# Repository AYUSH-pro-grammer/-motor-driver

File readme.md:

# STM32 Four Motor Driver

In my motor driver board, there is an STM32G431CBU6 with eight BTS7960B ICs to drive the four brushed DC motors.
I designed the circuit schematic and 4-layer PCB in KiCad, put artwork on both sides and wrote a simple Arduino sketch to check the hardware for the first time.

The repository contains the circuit schematic, PCB layout, Gerber files, parts list and demo firmware.
The board is currently in the design phase and needs to be assembled and tested.

## how it works

Each motor is connected between the outputs of two BTS7960B half-bridges
The STM32 provides one PWM signal and two direction signals per channel, which are combined using SN74ACT08 gates before going to the driver's inputs

The battery for the motors is plugged in via the XT60 connector, whereas the logic input is fed from 5V_IN
AMS1117-3.3 generates 3V3_MCU power supply for STM32

~~~text
STM32 PWM + direction --> SN74ACT08 gates --> BTS7960B pairs --> four motors
battery input --> motor supply
logic input --> 5V_IN --> AMS1117-3.3 --> STM32
encoder headers --> STM32
STM32 --> UART, I2C and external CAN transceiver header
~~~

there are four encoder connectors, a battery voltage divider, and three status LEDs in the circuit diagram.
the CAN bus requires a header connector that connects to an external transceiver module, but it is yet to be chosen.

## main features

- Four channels of motor control with two BTS7960B ICs on each channel
- Bare STM32G431CBU6 microcontroller in QFN packaging
- Two SN74ACT08 logic ICs for PWM and direction control of the motors
- 4-layer PCB approximately 162.5 x 57.4mm in size with a 1.6mm board thickness
- Screw terminal for motor outputs and XT60 footprint for battery input
- Connections to encoder, UART, I2C, and CAN module
- Front and back silkscreen printing
- UART controlled demo firmware with small motor pulses

## images

**full schematic**

**routed PCB**

**back artwork**

**angled board view**

these images are KiCad design previews, physical fit and operation still need checking on the assembled board

## how i plan to build it

1. check the supply connections, programming access and any remaining schematics and PCB checks
2. check that all BOM parts fit their footprints and select the regulator output capacitor
3. recreate and verify the Gerber and drill files following any modifications to the PCB
4. assemble the power and control boards and verify the supply rail voltages
5. program the demo using SWD and verify the control signals
6. test each motor channel one at a time using a current limited power supply

## firmware demo

open [motor_test.ino](firmware/motor_test/motor_test.ino) with the STM32duino Arduino core and select the generic STM32G431CBU board
the sketch uses the saved PCB pin mapping

| motor | PWM | direction 1 | direction 2 |
|---|---|---|---|
| A | PC6 | PB12 | PA10 |
| B | PB14 | PB15 | PB13 |
| C | PB4 | PB3 | PB5 |
| D | PA7 | PC4 | PB0 |

The UART console will use PB10 as TX and PB11 as RX at 115200 baud
Connect a 3.3 V USB-UART adapter where RX connects to PB10, TX to PB11 and GND to ground of the board

Send “a”, “b”, “c” or “d” to move forward and “A”, “B”, “C” or “D” to move backwards
Each command initiates one 500 ms pulse with a PWM value of 40/255 which is equal to 16%
Use “s” to stop before completion. The sketch begins with all outputs set to LOW

The demo sketch has yet to be compiled and tested on hardware, more tests with encoders and communication will be done later on

[STM32duino core and supported boards](https://github.com/stm32duino/Arduino_Core_STM32)

## what is in the repo

~~~text
.
├── firmware/motor_test/  Arduino motor test sketch
├── gerber/              PCB layers and drill files
├── gerber.zip           Fabrication archive
├── image/               Final project views and preserved originals
├── journal/             Individual devlogs and original screenshots
├── journal image/       Images used by the combined journal
├── kicad/               Schematic, PCB and project symbol library
├── bom.csv              Parts, quantities, prices and purchase links
├── JOURNAL.md           Combined development journal
└── readme.md            Project overview
~~~

## parts and BOM

the budget cost of the current parts is **$88.28 USD**, which includes the **PCB** at **$30.80** for five boards
the component totals refer to one board, while the orders include the quantities of components due to the vendor’s minimums
one 40-pin strip is ordered for cutting into eight headers

the prices are from the BOM estimates, with the conversion rate for ₹93.765 per USD for BTS7960
the shipping charges, additional taxes and the purchase of the C20 if necessary have to be added
C20 has a candidate link while the regulator compatibility check is underway

| board qty | order qty | part | unit price (USD) | cost (USD) | source |
|---:|---:|---|---:|---:|---|
| 11 | 50 | 100 nF 50 V X7R capacitor, 0805 | $0.0060 | $0.30 | [listing](https://www.lcsc.com/product-detail/C1711.html) |
| 4 | 4 | 1000 µF 25 V aluminum capacitor, SMD 10 × 10.5 mm | $0.4038 | $1.62 | [listing](https://www.lcsc.com/product-detail/C51018391.html) |
| 1 | 50 | 10 nF 50 V X7R capacitor, 0805 | $0.0116 | $0.58 | [listing](https://www.lcsc.com/product-detail/C1710.html) |
| 2 | 10 | 1 µF 50 V X7R capacitor, 0805 | $0.0403 | $0.40 | [listing](https://www.lcsc.com/product-detail/C28323.html) |
| 1 | 1 | 4.7 µF 25 V X5R capacitor, 0805 | $0.1300 | $0.13 | [listing](https://www.digikey.com/en/products/detail/samsung-electro-mechanics/CL21A475KAQNNNE/3889330) |
| 1 | pending | 22 µF output capacitor, 0805 | pending | pending | [listing](https://www.lcsc.com/product-detail/C602037.html) |
| 1 | 10 | 22 µF 25 V X5R input capacitor, 0805 | $0.1576 | $1.58 | [listing](https://www.lcsc.com/product-detail/C602037.html) |
| 6 | 6 | Red LED, 0805 | $0.2900 | $1.74 | [listing](https://www.digikey.com/en/products/detail/everlight-electronics-co-ltd/QTLP630C7TR/2675903) |
| 5 | 5 | Blue LED, 0805 | $0.3100 | $1.55 | [listing](https://www.digikey.com/en/products/detail/liteon/LTST-C170TBKT/388527) |
| 1 | 1 | Yellow LED, 0805 | $0.1800 | $0.18 | [listing](https://www.digikey.com/en/products/detail/lite-on-inc/LTST-C170KSKT/386781) |
| 1 | 1 | Green LED, 0805 | $0.1700 | $0.17 | [listing](https://www.digikey.com/en/products/detail/lite-on-inc/LTST-C170GKT/269251) |
| 1 | 5 | SMBJ18A unidirectional TVS diode, SMB | $0.1511 | $0.76 | [listing](https://www.lcsc.com/product-detail/C151256.html) |
| 1 | 10 | SS54B Schottky diode, SMB | $0.0486 | $0.49 | [listing](https://www.lcsc.com/product-detail/C2988643.html) |
| 4 | 4 | Phoenix Contact MKDS 3/2-5.08 motor terminal block | $1.9100 | $7.64 | [listing](https://us.rs-online.com/product/phoenix-contact/1711725/70054425/) |
| 1 | 1 | AMASS XT60PW-M right-angle PCB connector | $0.6054 | $0.61 | [listing](https://www.lcsc.com/product-detail/C98732.html) |
| 8 | 1 | 2.54 mm vertical pin headers, cut from one 40-pin strip | $0.4900 | $0.49 | [listing](https://www.digikey.com/en/products/detail/sullins-connector-solutions/PREC040SAAN-RC/2774814) |
| 1 | 1 | Phoenix Contact MKDS 1,5/2-5.08 5 V terminal block | $1.2800 | $1.28 | [listing](https://us.rs-online.com/product/phoenix-contact/1715721/70054416/) |
| 25 | 25 | 1 kΩ ±1% resistor, 0805 | $0.0256 | $0.64 | [listing](https://www.digikey.com/en/products/detail/yageo/RC0805FR-071KL/730391) |
| 22 | 100 | 10 kΩ ±1% resistor, 0805 | $0.0039 | $0.39 | [listing](https://www.lcsc.com/product-detail/C17414.html) |
| 3 | 100 | 220 Ω ±1% resistor, 0805 | $0.0055 | $0.55 | [listing](https://www.lcsc.com/product-detail/C17557.html) |
| 1 | 1 | 39 kΩ ±1% resistor, 0805 | $0.1000 | $0.10 | [listing](https://www.digikey.com/en/products/detail/yageo/RC0805FR-0739KL/727899) |
| 8 | 8 | BTS7960B half-bridge motor driver, TO-263-7 | $3.5866 | $28.69 | [listing](https://www.dnatechindia.com/bts7960-high-current-pn-half-bridge-ic-to263-buy-in-india.html) |
| 2 | 2 | TI SN74ACT08 quad AND gate, SOIC-14 | $0.5100 | $1.02 | [listing](https://www.digikey.com/en/products/detail/texas-instruments/SN74ACT08DR/404868) |
| 1 | 1 | STM32G431CBU6 microcontroller, UFQFPN-48 | $6.0800 | $6.08 | [listing](https://www.digikey.com/en/products/detail/stmicroelectronics/STM32G431CBU6/10231569) |
| 1 | 10 | UMW AMS1117-3.3 regulator, SOT-223 | $0.0486 | $0.49 | [listing](https://www.lcsc.com/product-detail/C347222.html) |
| — | 1 | JLCPCB PCB fabrication | $30.8000 | $30.80 | [listing](https://jlcpcb.com/) |
| | | **total for priced items** | | **$88.28** | |

## PCB files and current checks

- [KiCad project](kicad/Untitled.kicad_pro)
- [schematic](kicad/Untitled.kicad_sch)
- [PCB layout](kicad/Untitled.kicad_pcb)
- [project symbol library](kicad/Motor_Driver.kicad_sym)
- [Gerber and drill archive](gerber.zip)
- [individual fabrication files](gerber/)

## reference

i used the STM32G431CBU6 motor driver schematic by Rido Alin F, shown in the EasyEDA reference, as the starting point
my KiCad version uses the bare STM32 chip, with its power wiring and the PCB layout recorded in the journal
# -motor-driver

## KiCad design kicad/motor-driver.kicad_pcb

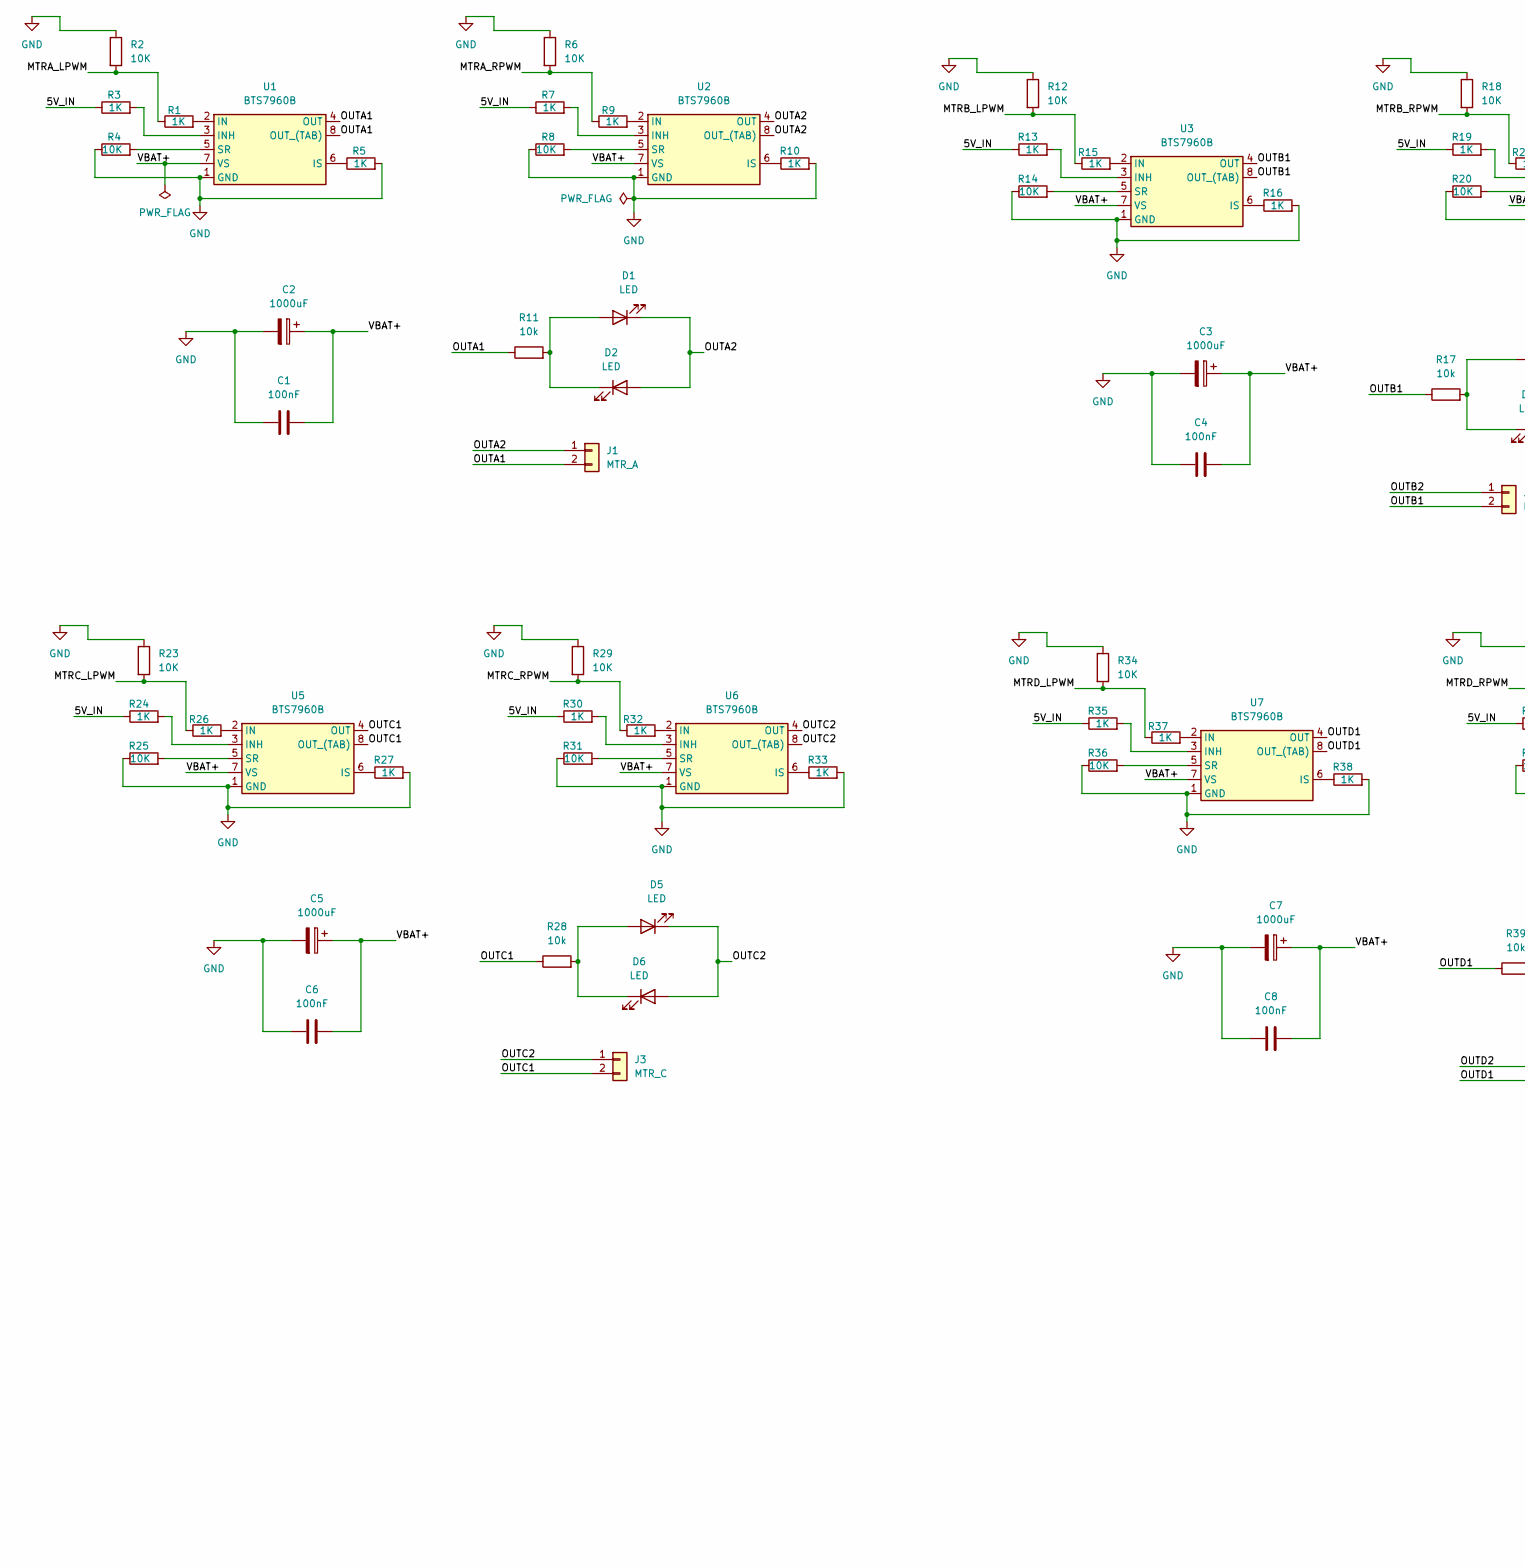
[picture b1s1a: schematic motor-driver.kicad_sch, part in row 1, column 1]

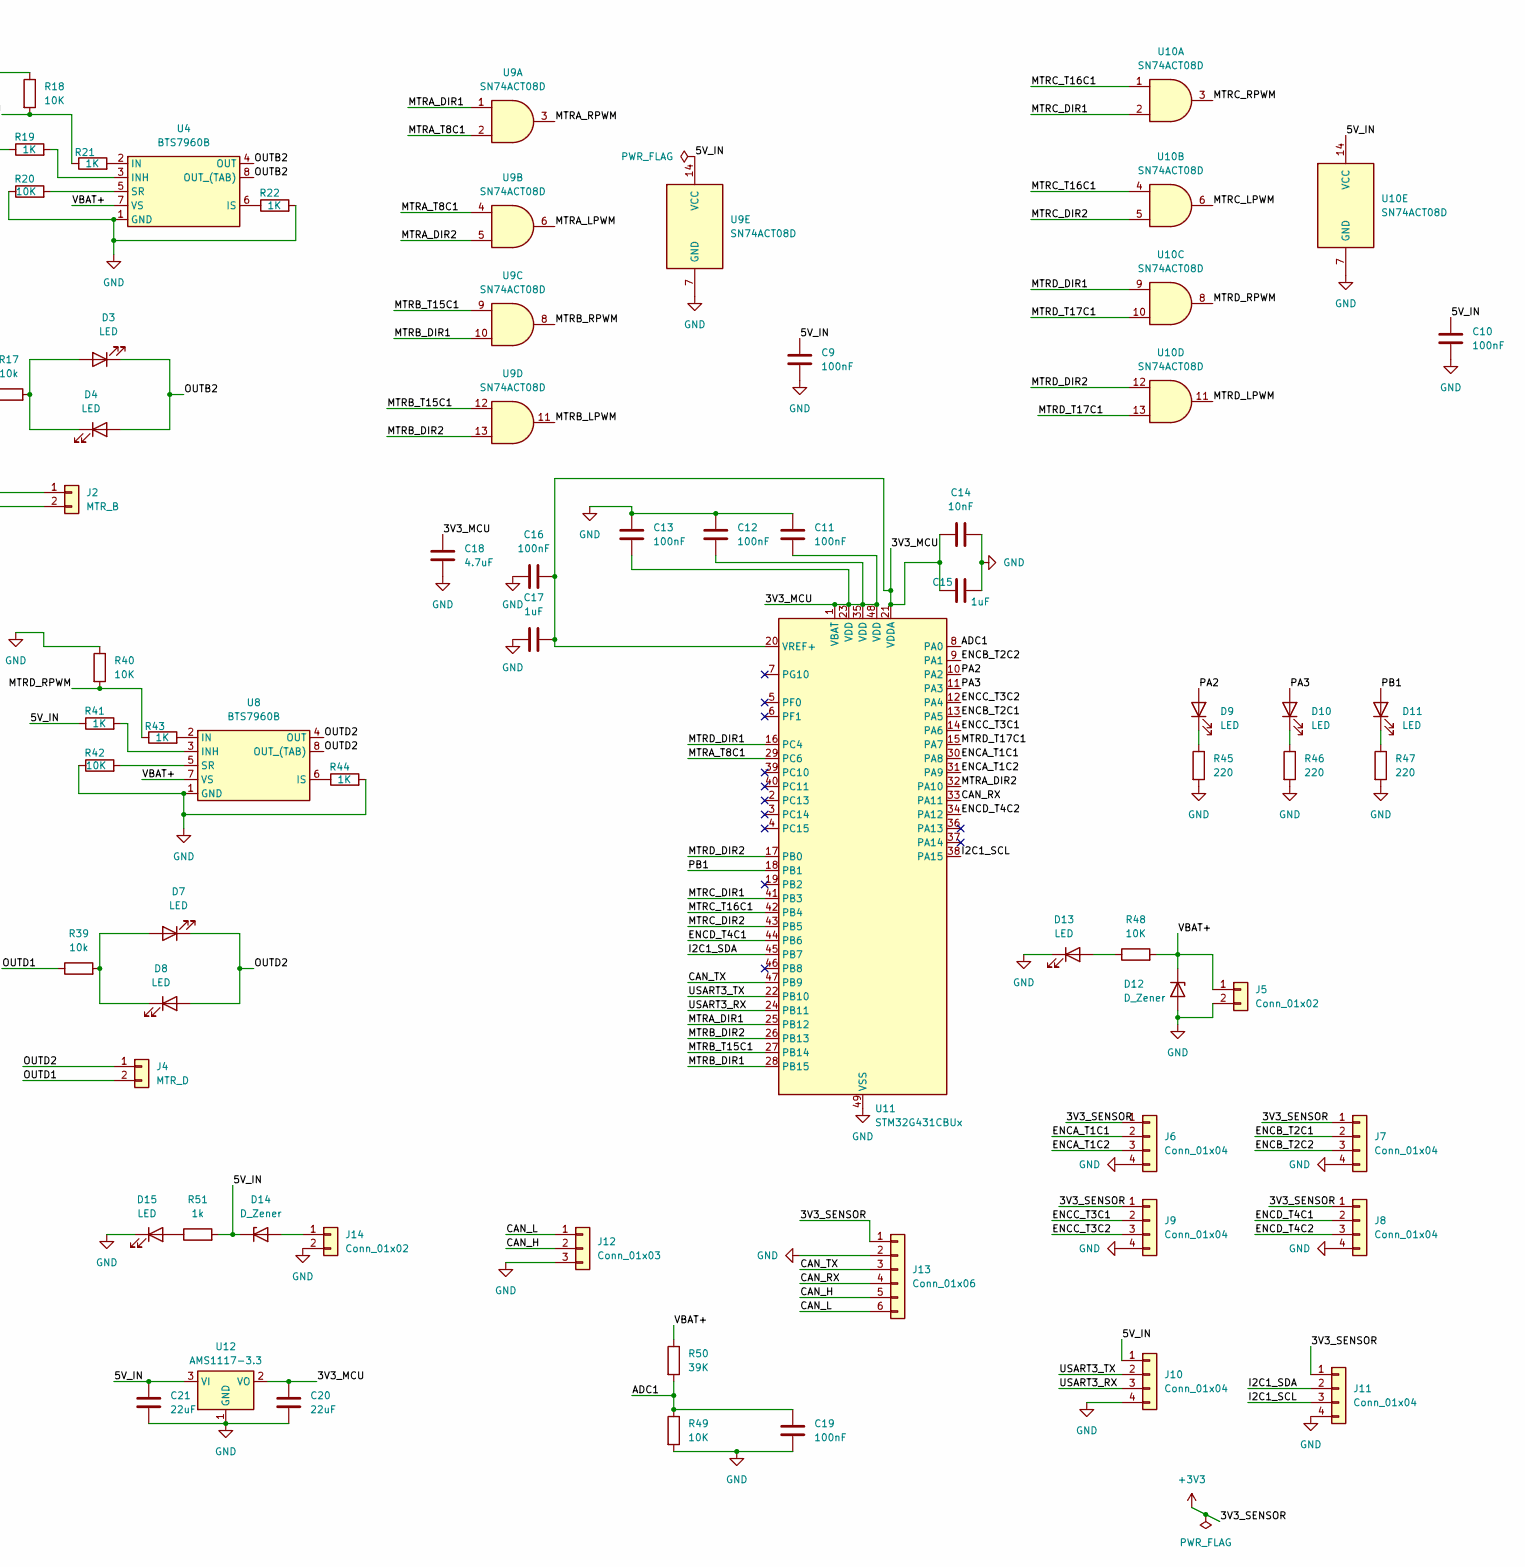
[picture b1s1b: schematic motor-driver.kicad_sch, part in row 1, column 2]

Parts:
C1, C4, C6, C8, C9, C10, C11, C12, C13, C16, C19: 100nF; C_0805_2012Metric
C2, C3, C5, C7: 1000uF; CP_Elec_10x10.5
C14: 10nF; C_0805_2012Metric
C15, C17: 1uF; C_0805_2012Metric
C18: 4.7uF; C_0805_2012Metric
C20, C21: 22uF; C_0805_2012Metric
D1, D2, D3, D4, D5, D6, D7, D8, D9, D10, D11, D13, D15: LED; LED_0805_2012Metric
D12, D14: D_Zener; D_SMB
J1: MTR_A; TerminalBlock_Phoenix_MKDS-3-2-5.08_1x02_P5.08mm_Horizontal
J2: MTR_B; TerminalBlock_Phoenix_MKDS-3-2-5.08_1x02_P5.08mm_Horizontal
J3: MTR_C; TerminalBlock_Phoenix_MKDS-3-2-5.08_1x02_P5.08mm_Horizontal
J4: MTR_D; TerminalBlock_Phoenix_MKDS-3-2-5.08_1x02_P5.08mm_Horizontal
J5: Conn_01x02; AMASS_XT60PW-M_1x02_P7.20mm_Horizontal
J6, J7, J8, J9, J10, J11: Conn_01x04; PinHeader_1x04_P2.54mm_Vertical
J12: Conn_01x03; PinHeader_1x03_P2.54mm_Vertical
J13: Conn_01x06; PinHeader_1x06_P2.54mm_Vertical
J14: Conn_01x02; TerminalBlock_Phoenix_MKDS-1,5-2-5.08_1x02_P5.08mm_Horizont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
R1, R3, R5, R7, R9, R10, R13, R15, R16, R19, R21, R22, R24, R26, R27, R30, R32, R33, R35, R37, R38, R41, R43, R44: 1K; R_0805_2012Metric
R2, R4, R6, R8, R12, R14, R18, R20, R23, R25, R29, R31, R34, R36, R40, R42, R48, R49: 10K; R_0805_2012Metric
R11, R17, R28, R39: 10k; R_0805_2012Metric
R45, R46, R47: 220; R_0805_2012Metric
R50: 39K; R_0805_2012Metric
R51: 1k; R_0805_2012Metric
U1, U2, U3, U4, U5, U6, U7, U8: BTS7960B; TO-263-7_TabPin8
U9, U10: SN74ACT08D; SOIC-14_3.9x8.7mm_P1.27mm
U11: STM32G431CBUx; QFN-48-1EP_7x7mm_P0.5mm_EP5.6x5.6mm
U12: AMS1117-3.3; SOT-223-3_TabPin2

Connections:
+3V3: J6.1, J7.1, J8.1, J9.1, J11.1, J13.1
/3V3_MCU: C11.2, C12.2, C13.2, C14.1, C15.1, C16.2, C17.2, C18.1, C20.1, U11.1 (VBAT), U11.20 (VREF+), U11.21 (VDDA), U11.23 (VDD), U11.35 (VDD), U11.48 (VDD), U12.2 (VO)
/5V_IN: C9.1, C10.1, C21.1, D14.1 (K), J10.1, R3.1, R7.1, R13.1, R19.1, R24.1, R30.1, R35.1, R41.1, R51.2, U9.14 (VCC), U10.14 (VCC), U12.3 (VI)
/ADC1: C19.1, R49.1, R50.2, U11.8 (PA0)
/CAN_H: J12.2, J13.5
/CAN_L: J12.1, J13.6
/CAN_RX: J13.4, U11.33 (PA11)
/CAN_TX: J13.3, U11.47 (PB9)
/ENCA_T1C1: J6.2, U11.30 (PA8)
/ENCA_T1C2: J6.3, U11.31 (PA9)
/ENCB_T2C1: J7.2, U11.13 (PA5)
/ENCB_T2C2: J7.3, U11.9 (PA1)
/ENCC_T3C1: J9.2, U11.14 (PA6)
/ENCC_T3C2: J9.3, U11.12 (PA4)
/ENCD_T4C1: J8.2, U11.44 (PB6)
/ENCD_T4C2: J8.3, U11.34 (PA12)
/I2C1_SCL: J11.3, U11.38 (PA15)
/I2C1_SDA: J11.2, U11.45 (PB7)
/MTRA_DIR1: U9.1, U11.25 (PB12)
/MTRA_DIR2: U9.5, U11.32 (PA10)
/MTRA_LPWM: R1.1, R2.2, U9.6
/MTRA_RPWM: R6.2, R9.1, U9.3
/MTRA_T8C1: U9.2, U9.4, U11.29 (PC6)
/MTRB_DIR1: U9.10, U11.28 (PB15)
/MTRB_DIR2: U9.13, U11.26 (PB13)
/MTRB_LPWM: R12.2, R15.1, U9.11
/MTRB_RPWM: R18.2, R21.1, U9.8
/MTRB_T15C1: U9.9, U9.12, U11.27 (PB14)
/MTRC_DIR1: U10.2, U11.41 (PB3)
/MTRC_DIR2: U10.5, U11.43 (PB5)
/MTRC_LPWM: R23.2, R26.1, U10.6
/MTRC_RPWM: R29.2, R32.1, U10.3
/MTRC_T16C1: U10.1, U10.4, U11.42 (PB4)
/MTRD_DIR1: U10.9, U11.16 (PC4)
/MTRD_DIR2: U10.12, U11.17 (PB0)
/MTRD_LPWM: R34.2, R37.1, U10.11
/MTRD_RPWM: R40.2, R43.1, U10.8
/MTRD_T17C1: U10.10, U10.13, U11.15 (PA7)
/OUTA1: J1.2, R11.1, U1.4 (OUT), U1.8 (OUT_(TAB))
/OUTA2: D1.1 (K), D2.2 (A), J1.1, U2.4 (OUT), U2.8 (OUT_(TAB))
/OUTB1: J2.2, R17.1, U3.4 (OUT), U3.8 (OUT_(TAB))
/OUTB2: D3.1 (K), D4.2 (A), J2.1, U4.4 (OUT), U4.8 (OUT_(TAB))
/OUTC1: J3.2, R28.1, U5.4 (OUT), U5.8 (OUT_(TAB))
/OUTC2: D5.1 (K), D6.2 (A), J3.1, U6.4 (OUT), U6.8 (OUT_(TAB))
/OUTD1: J4.2, R39.1, U7.4 (OUT), U7.8 (OUT_(TAB))
/OUTD2: D7.1 (K), D8.2 (A), J4.1, U8.4 (OUT), U8.8 (OUT_(TAB))
/PA2: D9.2 (A), U11.10 (PA2)
/PA3: D10.2 (A), U11.11 (PA3)
/PB1: D11.2 (A), U11.18 (PB1)
/USART3_RX: J10.3, U11.24 (PB11)
/USART3_TX: J10.2, U11.22 (PB10)
/VBAT+: C1.2, C2.1, C3.1, C4.2, C5.1, C6.2, C7.1, C8.2, D12.1 (K), J5.1, R48.2, R50.1, U1.7 (VS), U2.7 (VS), U3.7 (VS), U4.7 (VS), U5.7 (VS), U6.7 (VS), U7.7 (VS), U8.7 (VS)
GND: C1.1, C2.2, C3.2, C4.1, C5.2, C6.1, C7.2, C8.1, C9.2, C10.2, C11.1, C12.1, C13.1, C14.2, C15.2, C16.1, C17.1, C18.2, C19.2, C20.2, C21.2, D12.2 (A), D13.1 (K), D15.1 (K), J5.2, J6.4, J7.4, J8.4, J9.4, J10.4, J11.4, J12.3, J13.2, J14.2, R2.1, R4.1, R5.2, R6.1, R8.1, R10.2, R12.1, R14.1, R16.2, R18.1, R20.1, R22.2, R23.1, R25.1, R27.2, R29.1, R31.1, R33.2, R34.1, R36.1, R38.2, R40.1, R42.1, R44.2, R45.2, R46.2, R47.2, R49.2, U1.1 (GND), U2.1 (GND), U3.1 (GND), U4.1 (GND), U5.1 (GND), U6.1 (GND), U7.1 (GND), U8.1 (GND), U9.7 (GND), U10.7 (GND), U11.49 (VSS), U12.1 (GND)
unnamed: D1.2 (A), D2.1 (K), R11.2
unnamed: D3.2 (A), D4.1 (K), R17.2
unnamed: D5.2 (A), D6.1 (K), R28.2
unnamed: D7.2 (A), D8.1 (K), R39.2
unnamed: D9.1 (K), R45.1
unnamed: D10.1 (K), R46.1
unnamed: D11.1 (K), R47.1
unnamed: D13.2 (A), R48.1
unnamed: D14.2 (A), J14.1
unnamed: D15.2 (A), R51.1
unnamed: R1.2, U1.2 (IN)
unnamed: R3.2, U1.3 (INH)
unnamed: R5.1, U1.6 (IS)
unnamed: R4.2, U1.5 (SR)
unnamed: R9.2, U2.2 (IN)
unnamed: R7.2, U2.3 (INH)
unnamed: R10.1, U2.6 (IS)
unnamed: R8.2, U2.5 (SR)
unnamed: R15.2, U3.2 (IN)
unnamed: R13.2, U3.3 (INH)
unnamed: R16.1, U3.6 (IS)
unnamed: R14.2, U3.5 (SR)
unnamed: R21.2, U4.2 (IN)
unnamed: R19.2, U4.3 (INH)
unnamed: R22.1, U4.6 (IS)
unnamed: R20.2, U4.5 (SR)
unnamed: R26.2, U5.2 (IN)
unnamed: R24.2, U5.3 (INH)
unnamed: R27.1, U5.6 (IS)
unnamed: R25.2, U5.5 (SR)
unnamed: R32.2, U6.2 (IN)
unnamed: R30.2, U6.3 (INH)
unnamed: R33.1, U6.6 (IS)
unnamed: R31.2, U6.5 (SR)
unnamed: R37.2, U7.2 (IN)
unnamed: R35.2, U7.3 (INH)
unnamed: R38.1, U7.6 (IS)
unnamed: R36.2, U7.5 (SR)
unnamed: R43.2, U8.2 (IN)
unnamed: R41.2, U8.3 (INH)
unnamed: R44.1, U8.6 (IS)
unnamed: R42.2, U8.5 (SR)

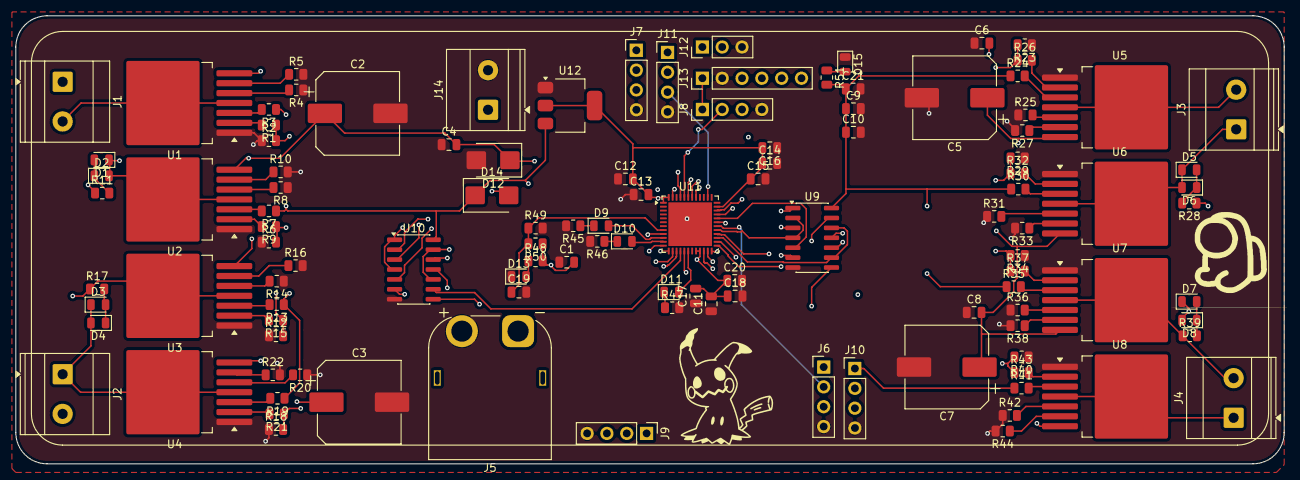
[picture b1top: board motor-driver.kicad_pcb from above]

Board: 4 copper layers, 162.5 x 57.4 mm, 113 parts (0 on the bottom side), 95 nets.

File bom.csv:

Name,References,Quantity,Order quantity,Unit price (USD),Total price (USD),Purchase link,Reference BOM link,Notes
"100 nF 50 V X7R capacitor, 0805","C1,C4,C6,C8,C9,C10,C11,C12,C13,C16,C19",11,50,0.0060,0.30,https://www.lcsc.com/product-detail/C1711.html,,
"1000 µF 25 V aluminum capacitor, SMD 10 × 10.5 mm","C2,C3,C5,C7",4,4,0.4038,1.62,https://www.lcsc.com/product-detail/C51018391.html,,Budget candidate. Verify VBAT transients and ripple rating before ordering. The SMBJ18A can clamp above 25 V.
"10 nF 50 V X7R capacitor, 0805",C14,1,50,0.0116,0.58,https://www.lcsc.com/product-detail/C1710.html,,
"1 µF 50 V X7R capacitor, 0805","C15,C17",2,10,0.0403,0.40,https://www.lcsc.com/product-detail/C28323.html,,
"4.7 µF 25 V X5R capacitor, 0805",C18,1,1,0.1300,0.13,https://www.digikey.com/en/products/detail/samsung-electro-m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,,
"22 µF output capacitor, 0805",C20,1,,,,https://www.lcsc.com/product-detail/C602037.html,https://www.lcsc.com/product-detail/C602037.html,"Candidate only. Verify effective capacitance and ESR requirements for the selected AMS1117-3.3. If compatible, use one from the C21 order."
"22 µF 25 V X5R input capacitor, 0805",C21,1,10,0.1576,1.58,https://www.lcsc.com/product-detail/C602037.html,https://www.lcsc.com/product-detail/C602037.html,
"Red LED, 0805","D1,D4,D6,D7,D13,D15",6,6,0.2900,1.74,https://www.digikey.com/en/products/detail/everlight-electro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,https://www.lcsc.com/product-detail/C2986044.html,Color assignment follows the reference schematic. KiCad uses generic LED values.
"Blue LED, 0805","D2,D3,D5,D8,D9",5,5,0.3100,1.55,https://www.digikey.com/en/products/detail/liteon/LTST-C170T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,,Check D9 brightness at the 3.3 V GPIO and selected resistor.
"Yellow LED, 0805",D10,1,1,0.1800,0.18,https://www.digikey.com/en/products/detail/lite-on-inc/LTST-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,,
"Green LED, 0805",D11,1,1,0.1700,0.17,https://www.digikey.com/en/products/detail/lite-on-inc/LTST-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,,
"SMBJ18A unidirectional TVS diode, SMB",D12,1,5,0.1511,0.76,https://www.lcsc.com/product-detail/C151256.html,https://www.lcsc.com/product-detail/C127556.html,VBAT protection per reference schematic. Check against the maximum supply voltage.
"SS54B Schottky diode, SMB",D14,1,10,0.0486,0.49,https://www.lcsc.com/product-detail/C2988643.html,,Series diode for the 5 V input. The reference SKU uses SMA. Verify logic rail headroom after the diode drop.
Phoenix Contact MKDS 3/2-5.08 motor terminal block,"J1,J2,J3,J4",4,4,1.9100,7.64,https://us.rs-online.com/product/phoenix-contact/1711725/70054425/,,Verify terminal and PCB current ratings for the motors.
AMASS XT60PW-M right-angle PCB connector,J5,1,1,0.6054,0.61,https://www.lcsc.com/product-detail/C98732.html,https://www.lcsc.com/product-detail/C7204007.html,
"2.54 mm vertical pin headers, cut from one 40-pin strip","J6,J7,J8,J9,J10,J11,J12,J13",8,1,0.4900,0.49,https://www.digikey.com/en/products/detail/sullins-connector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,https://www.lcsc.com/product-detail/C37208.html,"Cut six 4-pin, one 3-pin and one 6-pin section. Reference link is the individual 6-pin option for J13."
"Phoenix Contact MKDS 1,5/2-5.08 5 V terminal block",J14,1,1,1.2800,1.28,https://us.rs-online.com/product/phoenix-contact/1715721/70054416/,,
"1 kΩ ±1% resistor, 0805","R1,R3,R5,R7,R9,R10,R13,R15,R16,R19,R21,R22,R24,R26,R27,R30,R32,R33,R35,R37,R38,R41,R43,R44,R51",25,25,0.0256,0.64,https://www.digikey.com/en/products/detail/yageo/RC0805FR-07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,,
"10 kΩ ±1% resistor, 0805","R2,R4,R6,R8,R11,R12,R14,R17,R18,R20,R23,R25,R28,R29,R31,R34,R36,R39,R40,R42,R48,R49",22,100,0.0039,0.39,https://www.lcsc.com/product-detail/C17414.html,,
"220 Ω ±1% resistor, 0805","R45,R46,R47",3,100,0.0055,0.55,https://www.lcsc.com/product-detail/C17557.html,,
"39 kΩ ±1% resistor, 0805",R50,1,1,0.1000,0.10,https://www.digikey.com/en/products/detail/yageo/RC0805FR-07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,,
"BTS7960B half-bridge motor driver, TO-263-7","U1,U2,U3,U4,U5,U6,U7,U8",8,8,3.5866,28.69,https://www.dnatechindia.com/bts7960-high-current-pn-half-br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,https://jlcpcb.com/partdetail/InfineonTechnologies-BTS7960B/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,"Budget quote: ₹336.30 each including GST, converted at ₹93.765/USD. Confirm BTS7960B suffix with vendor."
"TI SN74ACT08 quad AND gate, SOIC-14","U9,U10",2,2,0.5100,1.02,https://www.digikey.com/en/products/detail/texas-instruments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,https://www.lcsc.com/product-detail/C2878686.html,SN74ACT08DR is the cut-tape option for the D package.
"STM32G431CBU6 microcontroller, UFQFPN-48",U11,1,1,6.0800,6.08,https://www.digikey.com/en/products/detail/stmicroelectronic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,,Bare MCU for the KiCad footprint.
"UMW AMS1117-3.3 regulator, SOT-223",U12,1,10,0.0486,0.49,https://www.lcsc.com/product-detail/C347222.html,https://www.lcsc.com/product-detail/C347222.html,
JLCPCB PCB fabrication,,,1,30.8000,30.80,https://jlcpcb.com/,,Price for one fabrication order
"TOTAL PRICE (USD, priced lines)",,113,,,88.28,,,"Includes PCB fabrication and listed order minimums."

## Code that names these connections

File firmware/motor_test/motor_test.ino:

#include <Arduino.h>

struct MotorPins {
  uint32_t pwm;
  uint32_t forward;
  uint32_t reverse;
};

const MotorPins motors[] = {
  {PC6, PB12, PA10},
  {PB14, PB15, PB13},
  {PB4, PB3, PB5},
  {PA7, PC4, PB0}
};

HardwareSerial console(PB11, PB10);
constexpr uint32_t pulseMs = 500;
constexpr uint8_t testDuty = 40;
uint32_t startedAt = 0;
bool running = false;
bool pwmReady = true;

void stopMotors() {
  for (const auto &motor : motors) {
    digitalWrite(motor.forward, LOW);
    digitalWrite(motor.reverse, LOW);
    analogWrite(motor.pwm, 0);
  }
  running = false;
}

void setup() {
  for (const auto &motor : motors) {
    digitalWrite(motor.forward, LOW);
    digitalWrite(motor.reverse, LOW);
    pinMode(motor.forward, OUTPUT);
    pinMode(motor.reverse, OUTPUT);
    digitalWrite(motor.pwm, LOW);
    pinMode(motor.pwm, OUTPUT);
    pwmReady = pwmReady && digitalPinHasPWM(motor.pwm);
  }
  analogWriteResolution(8);
  console.begin(115200);
  console.println("Motor test: a/b/c/d forward, A/B/C/D reverse, s stop");
  if (!pwmReady) {
    console.println("PWM pin mapping unavailable: select the generic STM32G431CBU board");
  }
}

void loop() {
  if (running && millis() - startedAt >= pulseMs) {
    stopMotors();
    console.println("Stopped");
  }
  if (!console.available()) {
    return;
  }
  const char command = console.read();
  if (command == '\r' || command == '\n') {
    return;
  }
  if (command == 's' || command == 'S') {
    stopMotors();
    return;
  }
  const bool forward = command >= 'a' && command <= 'd';
  const bool reverse = command >= 'A' && command <= 'D';
  if ((!forward && !reverse) || !pwmReady) {
    stopMotors();
    console.println("Invalid command or unavailable PWM");
    return;
  }
  if (running) {
    console.println("Wait for stop before another test");
    return;
  }
  const uint8_t index = forward ? command - 'a' : command - 'A';
  stopMotors();
  delay(100);
  digitalWrite(forward ? motors[index].forward : motors[index].reverse, HIGH);
  analogWrite(motors[index].pwm, testDuty);
  startedAt = millis();
  running = true;
  console.println("Testing for 500 ms");
}
